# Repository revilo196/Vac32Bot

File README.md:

# Vac32Bot

Clening roboter using STM32 and MBED

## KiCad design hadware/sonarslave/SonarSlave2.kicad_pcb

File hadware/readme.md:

# Used Hardware

## Body

As a base for the body this project was used <https://www.thingiverse.com/thing:2244952>

## Motion

- 2 MG995 servos as DC-motors for movement, hacked for continuous movement
- 2 Wheels with 40 2mm x 3mm x 1mm magnets
- 2 Hall-Effect Sensor boards as Wheel encoders
- Double Dual H-Bridge for controlling the DC-motors
- 2 INA219 current sensor modules

## Orientation

- 3 Ultrasonic distance sensors
- MPU9250 or MPU6500 for internal orientation measurement
- PMW3506 or similar for surface tacking
- EXPERIMENTAL 360 LIDAR for Testing

## Cleaning

- A2212 Brushless Motor powering the vacuum turbine
- ESC condoling the Brushless Motor
- DC-motor powering the floor brush

## Controller

- STM32F103C8T6(Blue Pill) managing the sonar sensor array
- STM32F446RE NUCLEO-64 as the main platform for the robot
- ESP32 or ESP8266 as wireless logger
- EXPERIMENTAL RaspberryPi analyzing LIDAR data

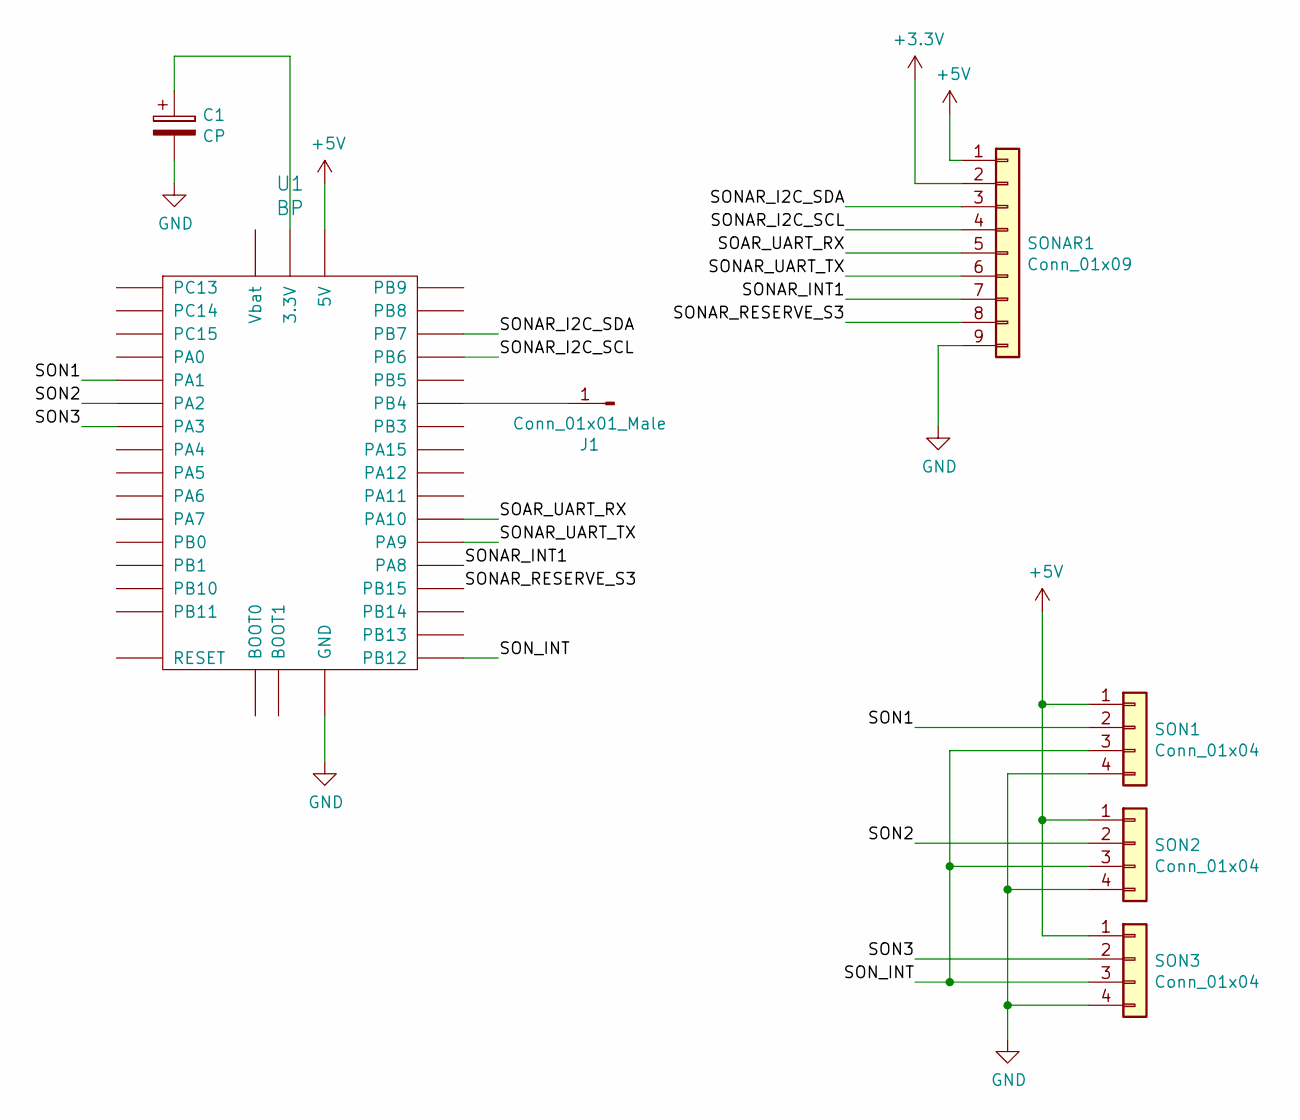
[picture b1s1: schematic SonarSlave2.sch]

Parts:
C1: CP; CP_Elec_5x5.3
J1: Conn_01x01_Male; PinHeader_1x01_P2.00mm_Vertical
SON1, SON2, SON3: Conn_01x04; JST_EH_B04B-EH-A_1x04_P2.50mm_Vertical
SONAR1: Conn_01x09; JST_EH_B09B-EH-A_1x09_P2.50mm_Vertical
U1: BP; BLUEPILL

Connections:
+3V3: SONAR1.2
+5V: SON1.1, SON2.1, SON3.1, SONAR1.1, U1.5V
/SOAR_UART_RX: SONAR1.5, U1.PA10
/SON1: SON1.2, U1.PA1
/SON2: SON2.2, U1.PA2
/SON3: SON3.2, U1.PA3
/SONAR_I2C_SCL: SONAR1.4, U1.PB6
/SONAR_I2C_SDA: SONAR1.3, U1.PB7
/SONAR_INT1: SONAR1.7, U1.PA8
/SONAR_RESERVE_S3: SONAR1.8, U1.PB15
/SONAR_UART_TX: SONAR1.6, U1.PA9
/SON_INT: SON1.3, SON2.3, SON3.3, U1.PB12
GND: C1.2, SON1.4, SON2.4, SON3.4, SONAR1.9, U1.G (GND)
unnamed: C1.1, U1.3V3 (3.3V)
unnamed: J1.1, U1.PB4

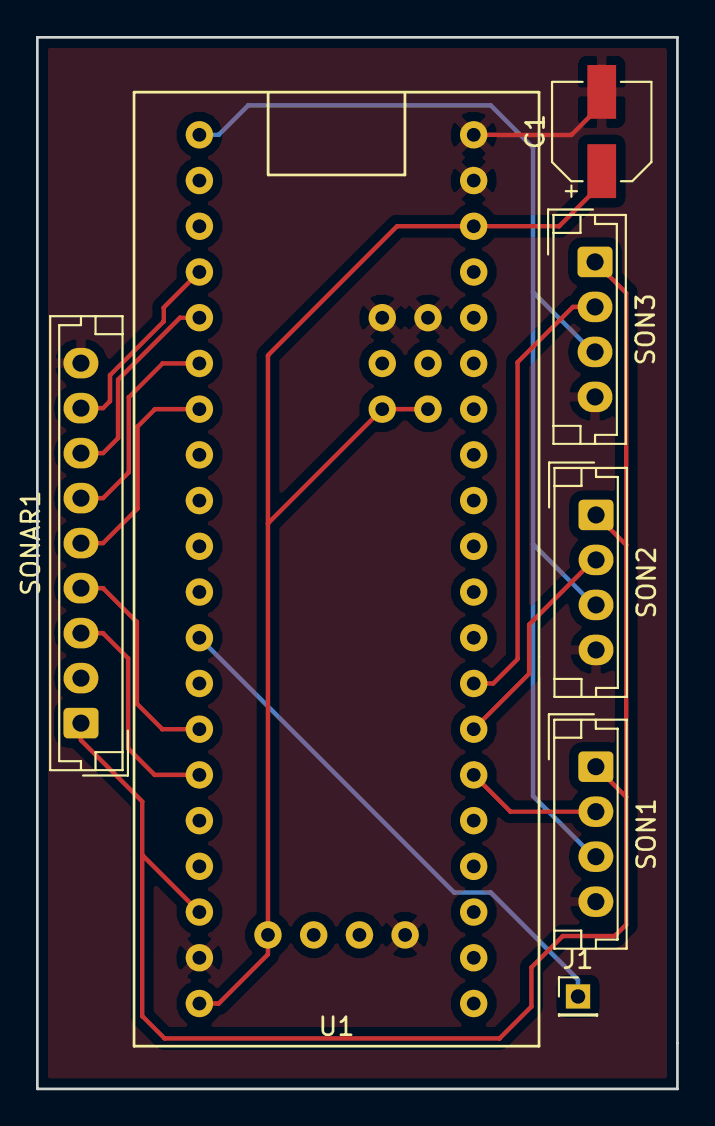
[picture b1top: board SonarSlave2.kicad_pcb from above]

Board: 2 copper layers, 35.6 x 58.4 mm, 7 parts (0 on the bottom side), 14 nets.

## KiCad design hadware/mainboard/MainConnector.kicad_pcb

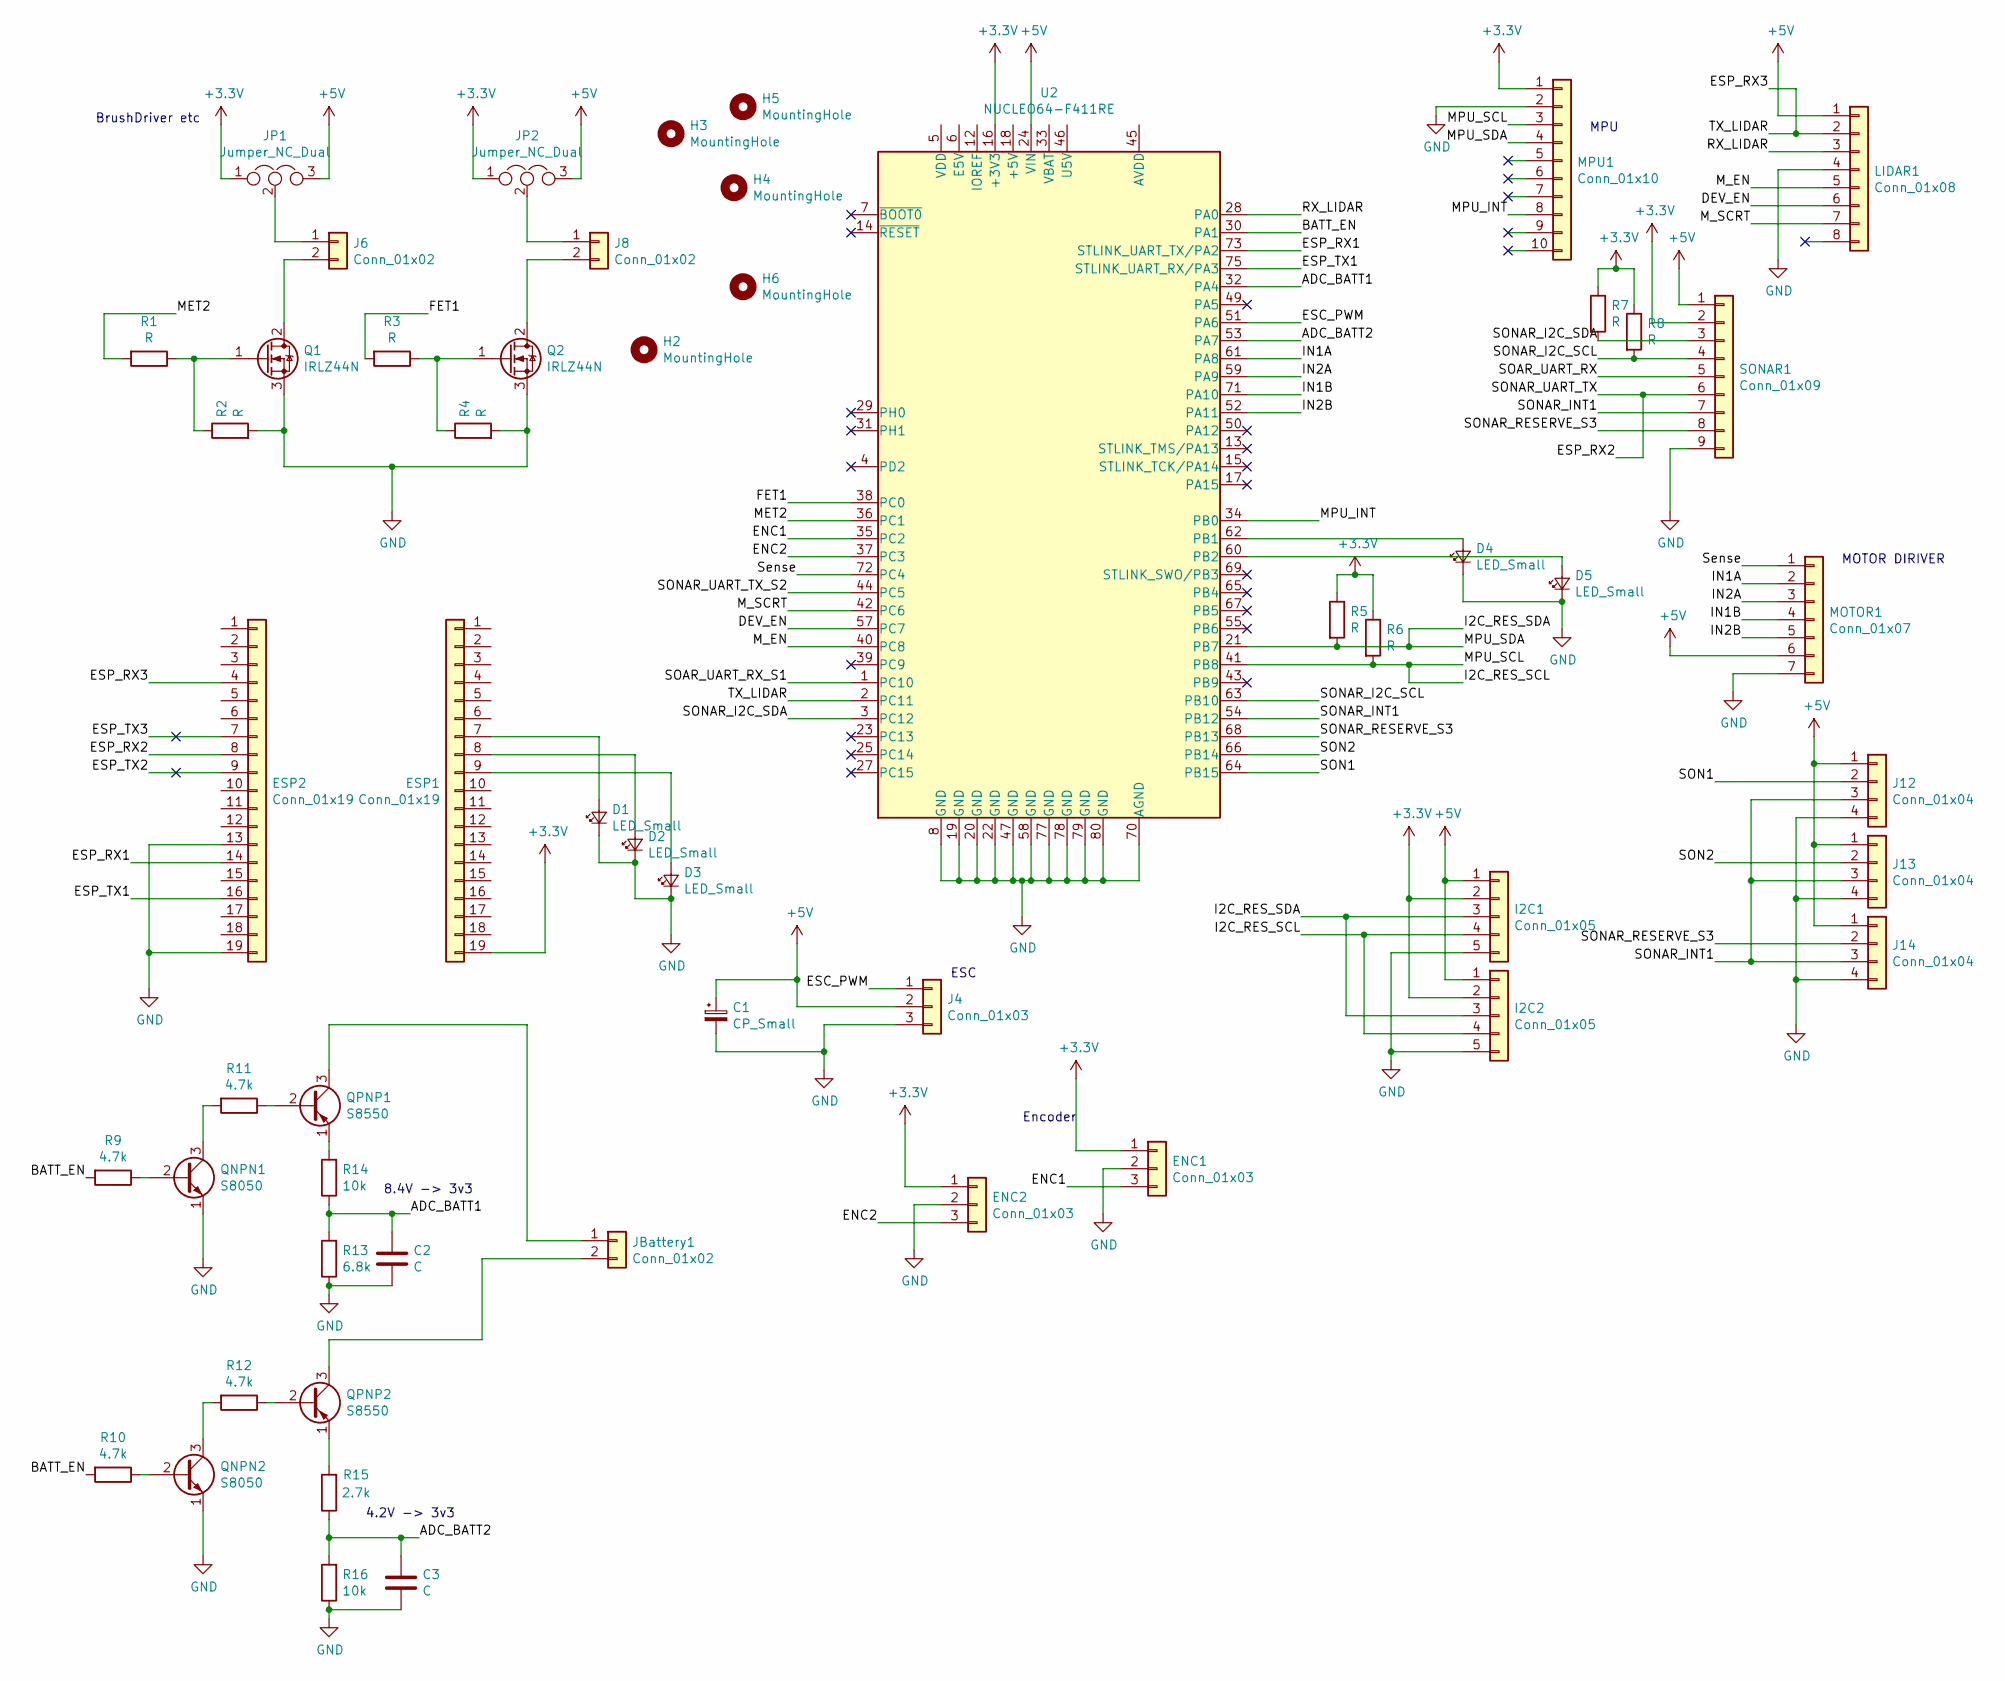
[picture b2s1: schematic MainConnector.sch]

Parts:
C1: CP_Small; CP_Elec_5x5.4
C2, C3: C; C_0805_2012Metric_Pad1.15x1.40mm_HandSolder
D1, D2, D3, D4, D5: LED_Small; LED_1206_3216Metric
ENC1, ENC2: Conn_01x03; JST_EH_B03B-EH-A_1x03_P2.50mm_Vertical
ESP1, ESP2: Conn_01x19; PinHeader_1x19_P2.54mm_Vertical
H2, H3, H4, H5, H6: MountingHole; MountingHole_3.2mm_M3
I2C1, I2C2: Conn_01x05; JST_EH_B05B-EH-A_1x05_P2.50mm_Vertical
J4: Conn_01x03; PinHeader_1x03_P2.54mm_Vertical
J6, J8: Conn_01x02; JST_EH_B02B-EH-A_1x02_P2.50mm_Vertical
J12, J13, J14: Conn_01x04; JST_EH_B04B-EH-A_1x04_P2.50mm_Vertical
JBattery1: Conn_01x02; JST_EH_B02B-EH-A_1x02_P2.50mm_Vertical
JP1, JP2: Jumper_NC_Dual; PinHeader_1x03_P2.54mm_Vertical
LIDAR1: Conn_01x08; JST_EH_B08B-EH-A_1x08_P2.50mm_Vertical
MOTOR1: Conn_01x07; JST_EH_B07B-EH-A_1x07_P2.50mm_Vertical
MPU1: Conn_01x10; JST_EH_B10B-EH-A_1x10_P2.50mm_Vertical
Q1, Q2: IRLZ44N; TO-220-3_Vertical
QNPN1, QNPN2: S8050; TO-92_Inline
QPNP1, QPNP2: S8550; TO-92_Inline
R1, R2, R3, R4, R5, R6, R7, R8: R; R_0805_2012Metric_Pad1.15x1.40mm_HandSolder
R9, R10, R11, R12: 4.7k; R_0805_2012Metric_Pad1.15x1.40mm_HandSolder
R13: 6.8k; R_0805_2012Metric_Pad1.15x1.40mm_HandSolder
R14, R16: 10k; R_0805_2012Metric_Pad1.15x1.40mm_HandSolder
R15: 2.7k; R_0805_2012Metric_Pad1.15x1.40mm_HandSolder
SONAR1: Conn_01x09; JST_EH_B09B-EH-A_1x09_P2.50mm_Vertical
U2: NUCLEO64-F411RE; ST_64_NUC

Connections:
+3V3: ENC1.1, ENC2.1, ESP1.19, I2C1.2, I2C2.2, JP1.1, JP2.1, MPU1.1, R5.1, R6.1, R7.1, R8.1, SONAR1.2, U2.16 (+3V3)
+5V: C1.1, I2C1.1, I2C2.1, J4.2, J12.1, J13.1, J14.1, JP1.3, JP2.3, LIDAR1.1, MOTOR1.6, SONAR1.1, U2.24 (VIN)
/ADC_BATT1: C2.1, R13.2, R14.1, U2.32 (PA4)
/ADC_BATT2: C3.1, R15.1, R16.2, U2.53 (PA7)
/BATT_EN: R9.2, R10.2, U2.30 (PA1)
/DEV_EN: LIDAR1.6, U2.57 (PC7)
/ENC1: ENC1.3, U2.35 (PC2)
/ENC2: ENC2.3, U2.37 (PC3)
/ESC_PWM: J4.1, U2.51 (PA6)
/ESP_RX1: ESP2.14, U2.73 (STLINK_UART_TX/PA2)
/ESP_RX2: ESP2.8, SONAR1.6
/ESP_RX3: ESP2.4, LIDAR1.2, U2.2 (PC11)
/ESP_TX1: ESP2.16, U2.75 (STLINK_UART_RX/PA3)
/ESP_TX2: ESP2.9
/ESP_TX3: ESP2.7
/FET1: R3.2, U2.38 (PC0)
/I2C_RES_SCL: I2C1.4, I2C2.4, MPU1.3, R6.2, U2.41 (PB8)
/I2C_RES_SDA: I2C1.3, I2C2.3, MPU1.4, R5.2, U2.21 (PB7)
/IN1A: MOTOR1.2, U2.61 (PA8)
/IN1B: MOTOR1.4, U2.71 (PA10)
/IN2A: MOTOR1.3, U2.59 (PA9)
/IN2B: MOTOR1.5, U2.52 (PA11)
/MET2: R1.2, U2.36 (PC1)
/MPU_INT: MPU1.8, U2.34 (PB0)
/M_EN: LIDAR1.5, U2.40 (PC8)
/M_SCRT: LIDAR1.7, U2.42 (PC6)
/RX_LIDAR: LIDAR1.3, U2.28 (PA0)
/SOAR_UART_RX: SONAR1.5
/SOAR_UART_RX_S1: U2.1 (PC10)
/SON1: J12.2, U2.64 (PB15)
/SON2: J13.2, U2.66 (PB14)
/SONAR_I2C_SCL: R8.2, SONAR1.4, U2.63 (PB10)
/SONAR_I2C_SDA: R7.2, SONAR1.3, U2.3 (PC12)
/SONAR_INT1: J12.3, J13.3, J14.3, SONAR1.7, U2.54 (PB12)
/SONAR_RESERVE_S3: J14.2, SONAR1.8, U2.68 (PB13)
/SONAR_UART_TX_S2: U2.44 (PC5)
/Sense: MOTOR1.1, U2.72 (PC4)
GND: C1.2, C2.2, C3.2, D1.1 (K), D2.1 (K), D3.1 (K), D4.1 (K), D5.1 (K), ENC1.2, ENC2.2, ESP2.13, ESP2.19, I2C1.5, I2C2.5, J4.3, J12.4, J13.4, J14.4, LIDAR1.4, MOTOR1.7, MPU1.2, Q1.3 (S), Q2.3 (S), QNPN1.1 (E), QNPN2.1 (E), R2.2, R4.2, R13.1, R16.1, SONAR1.9, U2.8 (GND), U2.19 (GND), U2.20 (GND), U2.22 (GND), U2.47 (GND), U2.58 (GND), U2.70 (AGND), U2.77 (GND), U2.78 (GND), U2.79 (GND), U2.80 (GND)
unnamed: D1.2 (A), ESP1.7
unnamed: D2.2 (A), ESP1.8
unnamed: D3.2 (A), ESP1.9
unnamed: D4.2 (A), U2.62 (PB1)
unnamed: D5.2 (A), U2.60 (PB2)
unnamed: J6.1, JP1.2
unnamed: J6.2, Q1.2 (D)
unnamed: J8.1, JP2.2
unnamed: J8.2, Q2.2 (D)
unnamed: JBattery1.1, QPNP1.3 (C)
unnamed: JBattery1.2, QPNP2.3 (C)
unnamed: Q1.1 (G), R1.1, R2.1
unnamed: Q2.1 (G), R3.1, R4.1
unnamed: QNPN1.2 (B), R9.1
unnamed: QNPN1.3 (C), R11.2
unnamed: QNPN2.2 (B), R10.1
unnamed: QNPN2.3 (C), R12.2
unnamed: QPNP1.1 (E), R14.2
unnamed: QPNP1.2 (B), R11.1
unnamed: QPNP2.1 (E), R15.2
unnamed: QPNP2.2 (B), R12.1

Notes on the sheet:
Encoder
ESC
MOTOR DIRIVER
MPU
BrushDriver etc
4.2V -> 3v3
8.4V -> 3v3

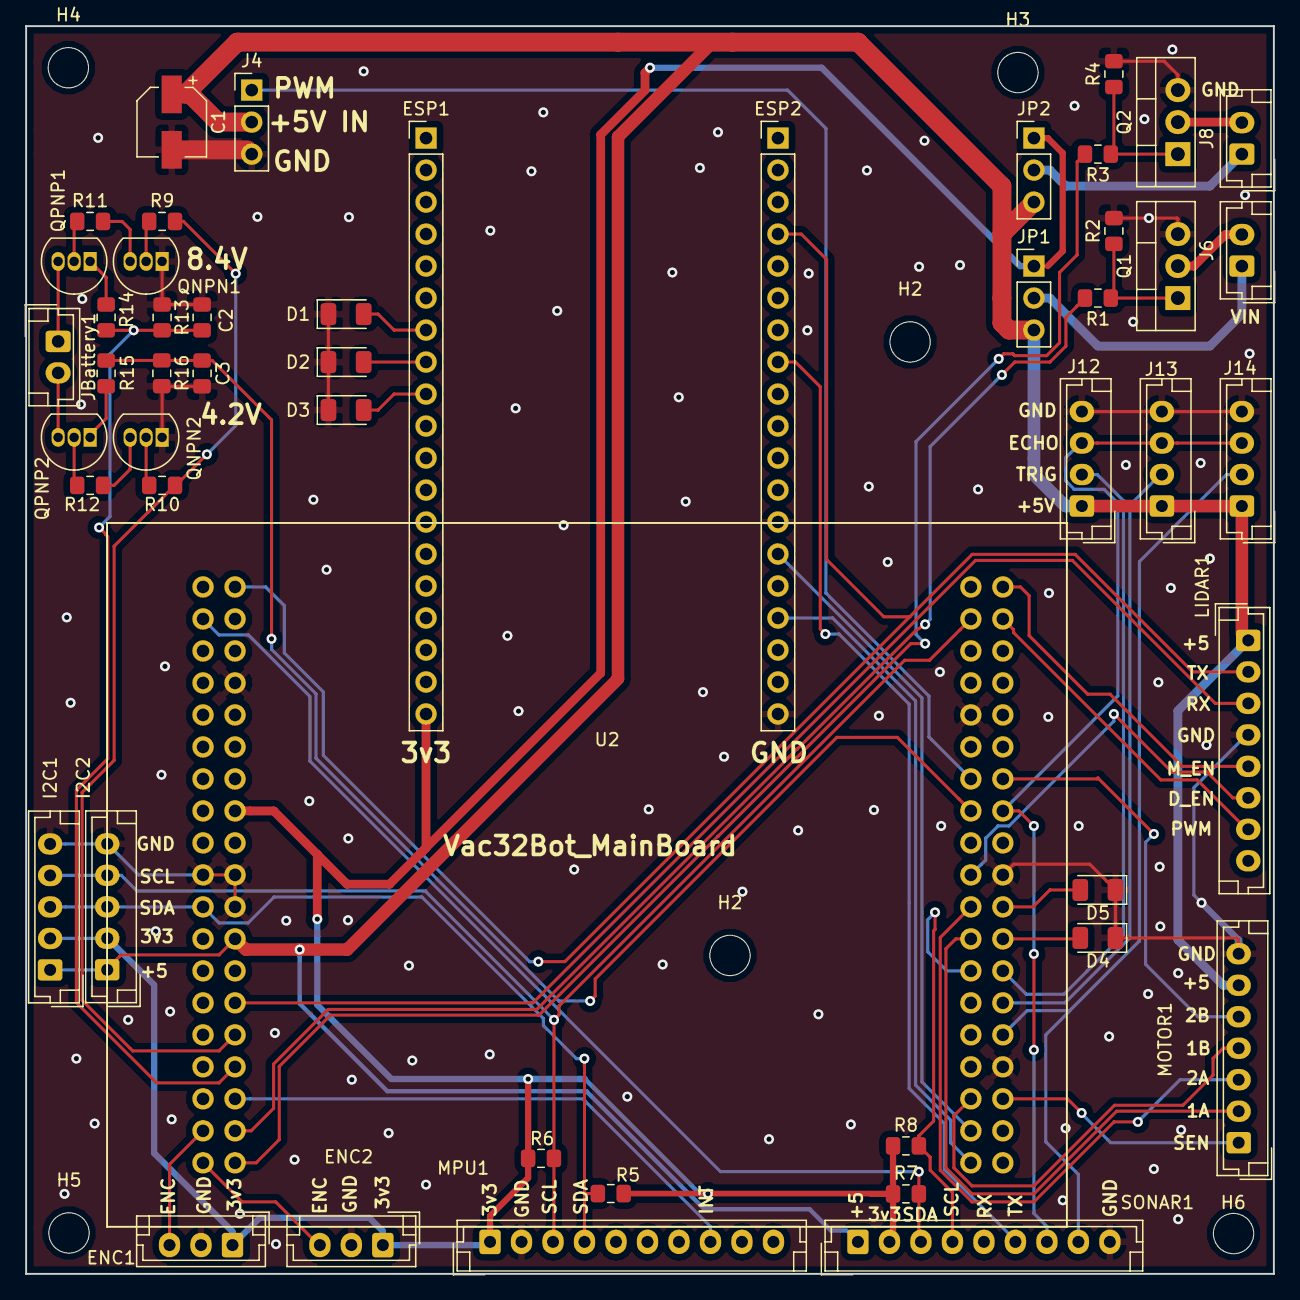
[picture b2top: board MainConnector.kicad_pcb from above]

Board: 2 copper layers, 99.1 x 99.1 mm, 56 parts (0 on the bottom side), 54 nets.

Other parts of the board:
H2#2: MountingHole; MountingHole_3.2mm_M3

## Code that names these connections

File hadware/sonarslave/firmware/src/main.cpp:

#include <Arduino.h>
#include <Wire.h>
#include <OneWire.h>
#include <DallasTemperature.h>
#include <HCSR04.h>
#include <cmath>

// Data wire is plugged into port 2 on the Arduino
#define ONE_WIRE_BUS PB10

// Setup a oneWire instance to communicate with any OneWire devices (not just Maxim/Dallas temperature ICs)
OneWire oneWire(ONE_WIRE_BUS);
// Pass our oneWire reference to Dallas Temperature. 
DallasTemperature sensors(&oneWire);
// arrays to hold device address
DeviceAddress insideThermometer;

TwoWire i2c(PB7,PB6);

#define s_cnt 3
#define buff_cnt 5
#define LED PC13

UltraSonicDistanceSensor sonars[s_cnt] = {
  UltraSonicDistanceSensor(PB13,PB12),
  UltraSonicDistanceSensor(PB14,PA11),
  UltraSonicDistanceSensor(PB15,PA12)
};



uint64_t counter = 0;
uint32_t values_mm[s_cnt];
uint32_t stdev_mm[s_cnt];
uint32_t sonar_buffer_counter[s_cnt];
uint32_t sonar_buffer[s_cnt][buff_cnt];
uint32_t temp_deviation[buff_cnt];
uint8_t cmd = 1;
float temp;
bool led_on = false;

void printAddress(DeviceAddress deviceAddress)
{
  for (uint8_t i = 0; i < 8; i++)
  {
    if (deviceAddress[i] < 16) Serial.print("0");
    Serial.print(deviceAddress[i], HEX);
  }
}

void onRecive(int howMany) {
  if (howMany > 0) {
  uint8_t * data = (uint8_t*)malloc(howMany);
  i2c.readBytes(data,howMany);
  cmd = data[0];
  free(data);
  }
  Serial.println("CMD RECIVED");
}

void onRequest(void) {
  switch (cmd)
  {
  case 1:
      i2c.write((const char*) values_mm, sizeof(uint32_t)*3);
    break;
  case 2:
      i2c.write((const char*) stdev_mm, sizeof(uint32_t)*3);
  default:
    i2c.write((const char*) values_mm, sizeof(uint32_t)*3);
    break;
  }
  Serial.println("RESPONSE SEND");
}

float getTemperature(){
  sensors.requestTemperatures();

  Serial.print(values_mm[0]);
  Serial.print(" ");
  Serial.print(values_mm[1]);
  Serial.print(" ");
  Serial.println(values_mm[2]);

  float tempC = sensors.getTempC(insideThermometer);
  Serial.print("Temp C: ");
  Serial.println(tempC);
  return tempC;
}

void setup() {
   //put your setup code here, to run once:
  Serial.begin(9600);
  
  i2c.begin(21);
  i2c.onRequest(&onRequest);
  i2c.onReceive(&onRecive);

  pinMode(LED, OUTPUT);

  Serial.print("Parasite power is: "); 
  if (sensors.isParasitePowerMode()) Serial.println("ON");
  else Serial.println("OFF");
  if (!sensors.getAddress(insideThermometer, 0)) Serial.println("Unable to find address for Device 0"); 
  Serial.print("Device 0 Address: ");
  printAddress(insideThermometer);
  Serial.println();
  // set the resolution to 9 bit (Each Dallas/Maxim device is capable of several different resolutions)
  sensors.setResolution(insideThermometer, 9);
  Serial.print("Device 0 Resolution: ");
  Serial.print(sensors.getResolution(insideThermometer), DEC); 
  Serial.println();

  //reset all buffers
  for (size_t i = 0; i < s_cnt; i++)
  {
    sonar_buffer_counter[i] = 0;
    values_mm[i] = 0;
    for (size_t j = 0; j < buff_cnt; j++)
    {
      sonar_buffer[i][j]=0;
    }
    
  }
  
  temp = getTemperature();
}

void loop() {
  if (counter % 500 == 0 ) {
    temp = getTemperature();
  }  
  int current = counter % 3;

  uint32_t value_um = sonars[current].measureDistanceCm(temp) * 10000;
  

  if (value_um > 1) {
    //insert new value into buffer
    uint32_t buffer_slot = sonar_buffer_counter[current];
    uint32_t  * buffer = sonar_buffer[current];
    buffer[buffer_slot] = value_um;
    sonar_buffer_counter[current] = (sonar_buffer_counter[current]+1) % buff_cnt;

    uint64_t sum = 0;
    for (size_t i = 0; i < buff_cnt; i++) {sum += buffer[i];}
    uint32_t mean = sum / buff_cnt;

    uint64_t vari_sum = 0;
    uint64_t max_vari = 0;
    uint64_t max_idx = 0;
    for (size_t i = 0; i < buff_cnt; i++)
    { 
      uint64_t var = sq(mean -  buffer[i]);
      if (var > max_vari) {
        max_vari = var;
        max_idx = i;
      }
      vari_sum += var; 
    }
    uint64_t vari = vari_sum /buff_cnt;

    if(vari > sq(20000)) {
      sum -= buffer[max_idx];
      mean = sum / (buff_cnt-1);
      vari_sum = 0;
      for (size_t i = 0; i < buff_cnt; i++)
      { 
        if(i == max_idx) {continue;}
        vari_sum += sq(mean -  buffer[i]);
      }
      vari = vari_sum / (buff_cnt-1);
    }
    values_mm[current] =  mean;
    stdev_mm[current] = sqrt(vari);

  } else {
    // no valid echo
  }

    Serial.print(values_mm[0]/1000);
    Serial.print(" \t ");
    Serial.print(values_mm[1]/1000);
    Serial.print(" \t ");
    Serial.println(values_mm[2]/1000);

  
  if (led_on) {
    digitalWrite(LED,LOW);
    led_on = false;
  } else {
    digitalWrite(LED,HIGH);
    led_on = true;
  }

  counter++;
}

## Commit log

2020-02-21 PID drive control
2020-02-21 Optical mouse senser
2020-02-23 arrays and doc
    now logging arrays
    documentation added
2020-02-23 calulate and filter velocity
2020-02-23 IMU advanced calibration
    advanced calibration calulcation bias, stdev,
    covariance and correlation of the 6 Axis
    and short re_calibration calculation new bias
2020-02-23 cleanup unused code
2020-02-23 calibration testing
2020-02-24 main cleanup
2020-02-24 hadware documentationadded board layoutsadded BOMadded sonar firmware
2020-02-24 removed PID controller
2020-02-24 fixing main for testing
2020-02-24 added logging tool
2020-02-28 logger abort error fix
2020-02-28 minor cleanup
2020-02-28 sonar system
2020-02-28 drive estimation output
2020-02-29 logger console control
    closes #1
2020-02-29 moved sensors into seperate libs
2020-03-01 drive current mesurement
2020-03-01 logger bytes
2020-03-01 drive to navi signal
    resolve #5
2020-03-01 increase PWM frequency
2020-03-01 pwm to 2kHz
2020-03-01 sonar obstical signal
    resolve #7
2020-03-02 IMU and Opt/Dirve Navigations Signals
    Implemented signals to the navigation system
    so that the navigation system
    gets informed when an error in dirving occurs
    like a crash or getting stuck
    resolve #9
    resolve #8
2020-03-06 Weekend commit #
